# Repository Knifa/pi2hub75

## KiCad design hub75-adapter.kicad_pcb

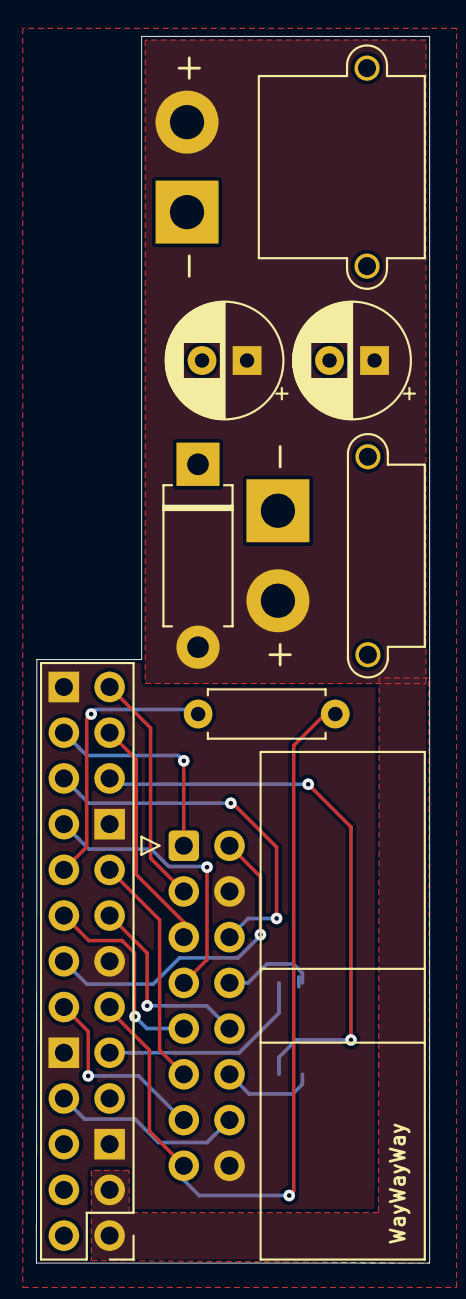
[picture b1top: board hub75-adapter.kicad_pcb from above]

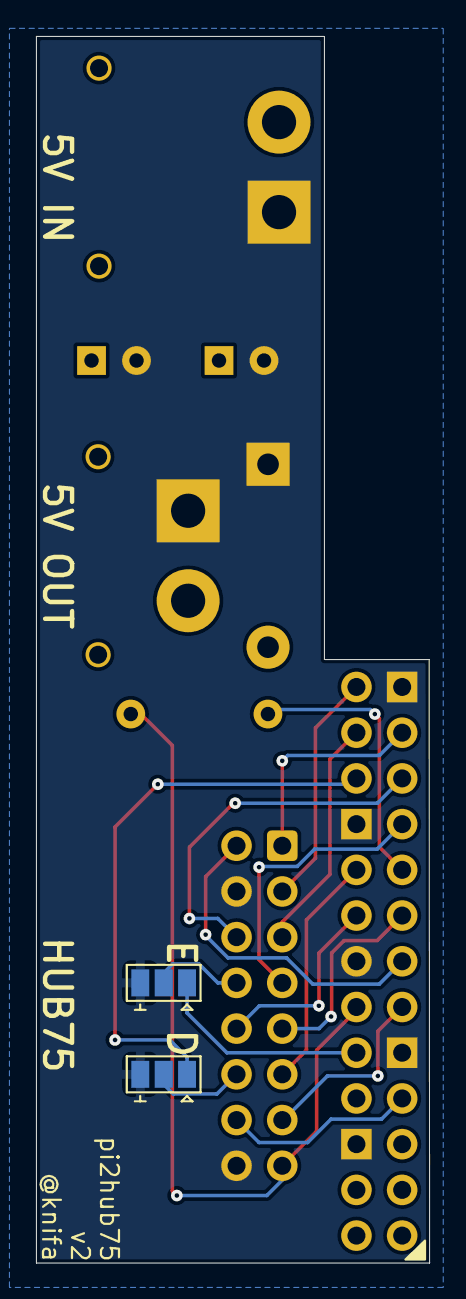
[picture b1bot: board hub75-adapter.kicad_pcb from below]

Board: 2 copper layers, 21.8 x 68.1 mm, 10 parts (2 on the bottom side), 19 nets.

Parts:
C2, C3: 330u; CP_Radial_D6.3mm_P2.50mm
D1: D_TVS; D_DO-15_P10.16mm_Horizontal
J1: PI; PiHeader
J2: 5V_IN; AMASS_XT30PW-M_1x02_P2.50mm_Horizontal
J3: HUB75; IDC-Header_2x08_P2.54mm_Horizontal
J4: 5V_OUT_MATRIX; AMASS_XT30PW-F_1x02_P2.50mm_Horizontal
JP1: E_EN; SolderJumper-3_P1.3mm_Bridged12_Pad1.0x1.5mm
JP2: D_EN; SolderJumper-3_P1.3mm_Bridged12_Pad1.0x1.5mm
R1: 10k; R_Axial_DIN0207_L6.3mm_D2.5mm_P7.62mm_Horizontal

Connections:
+3V3: J1.1 (3V3), J1.17 (3V3), R1.2
+5V: C2.1, C3.1, D1.2 (A2), J1.2 (5V), J1.4 (5V), J2.2, J4.2
/A: J1.15 (GPIO22), J3.9 (A)
/B: J1.16 (GPIO23), J3.10 (B)
/B0: J1.26 (~CE1/GPIO7), J3.3 (B0)
/B1: J1.19 (MOSI0/GPIO10), J3.7 (B1)
/C: J1.18 (GPIO24), J3.11 (C)
/CLK: J1.11 (GPIO17), J3.13 (CLK)
/D: J1.22 (GPIO25), JP2.1 (A)
/D_HUB75: J3.12 (D), JP2.2 (C)
/E: J1.10 (GPIO15/RXD), JP1.3 (B)
/E_HUB75: J3.8 (E), JP1.2 (C)
/G0: J1.13 (GPIO27), J3.2 (G0)
/G1: J1.21 (MISO0/GPIO9), J3.6 (G1)
/LAT: J1.7 (GCLK0/GPIO4), J3.14 (LAT)
/R0: J1.23 (SCLK0/GPIO11), J3.1 (R0)
/R1: J1.24 (~CE0/GPIO8), J3.5 (R1)
/~OE: J1.12 (GPIO18/PWM0), J3.15 (~OE), R1.1
GND: C2.2, C3.2, D1.1 (A1), J1.6 (GND), J1.9 (GND), J1.14 (GND), J1.20 (GND), J1.25 (GND), J2.1, J3.4 (GND), J3.16 (GND), J4.1, JP1.1 (A), JP2.3 (B)

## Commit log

2024-09-03 rev2 w/ oe resistor
